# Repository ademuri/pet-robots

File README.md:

# Pet Robots

Small household robots with personality.

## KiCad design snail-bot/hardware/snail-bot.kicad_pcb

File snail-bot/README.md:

I added support for the STM32G030F6 on Arduino to Platformio in [this commit](https://github.com/stm32duino/Arduino_Core_STM32/pull/1589). That change isn't in a release yet, so you'll need to manually update it:

```bash
cd /tmp
git clone https://github.com/stm32duino/Arduino_Core_STM32
cd Arduino_Core_STM32
git checkout 8c7db46
cp ./* "${HOME?}/.platformio/packages/framework-arduinoststm32/"
```

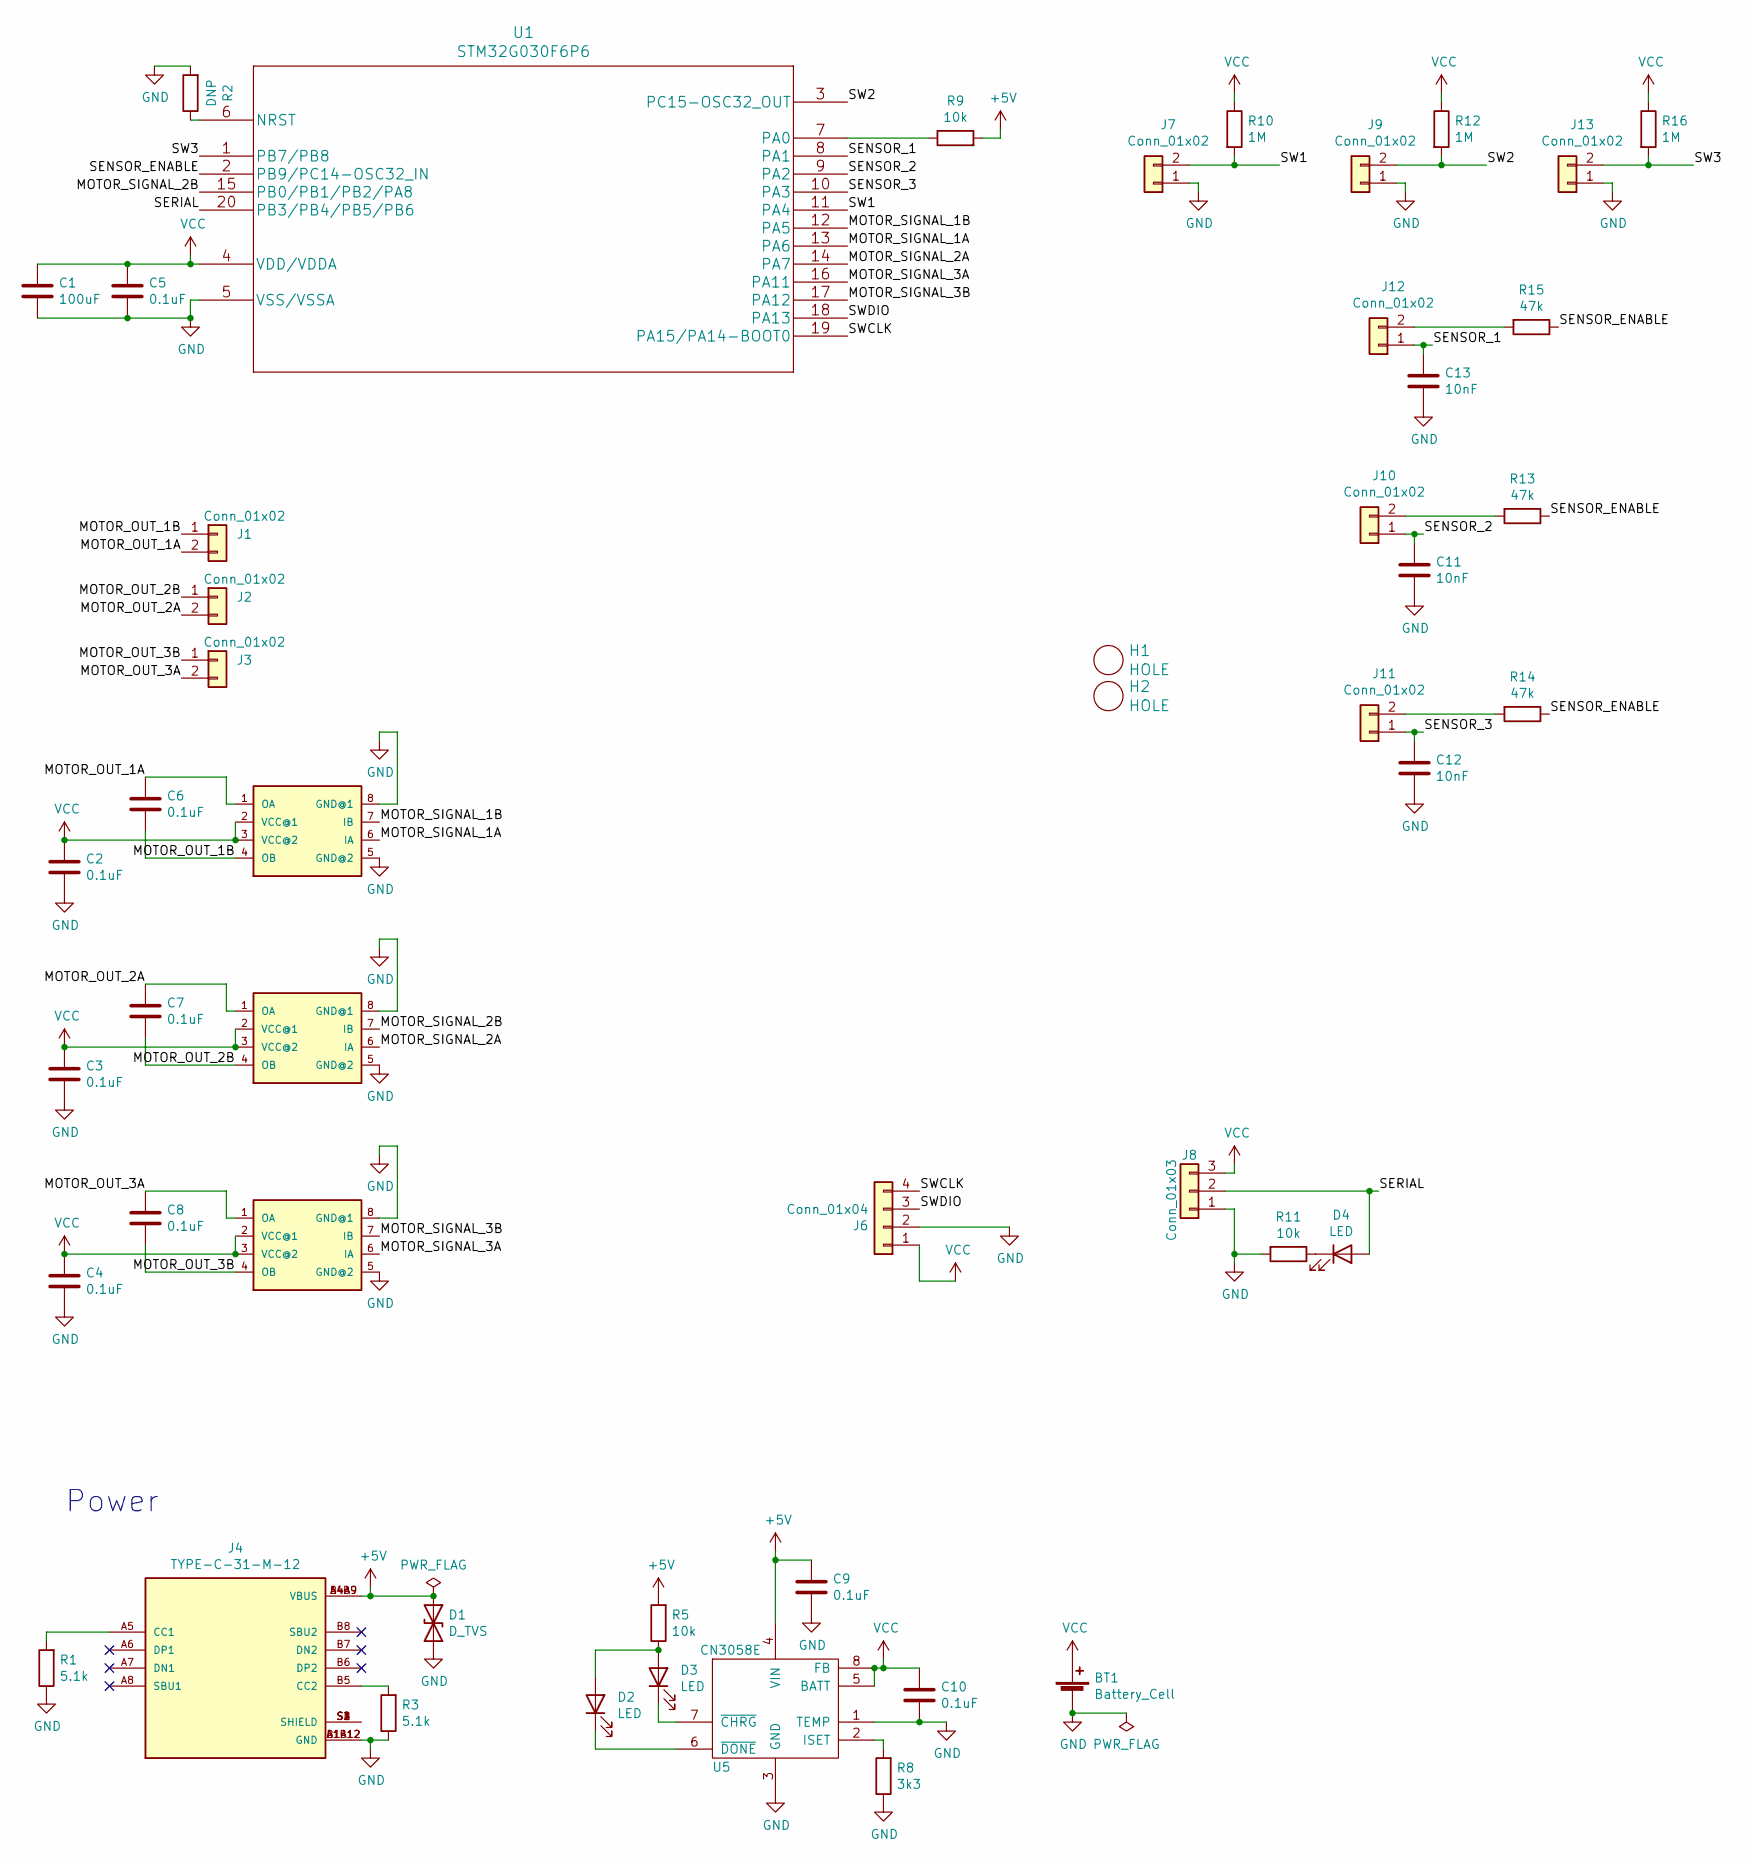
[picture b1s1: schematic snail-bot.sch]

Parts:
BT1: Battery_Cell; BatteryHolder_Keystone_2460_1xAA
C1: 100uF; C_1206_3216Metric; LCSC C15008
C2, C3, C4, C5, C6, C7, C8, C9, C10: 0.1uF; C_0603_1608Metric; LCSC C14663
C11, C12, C13: 10nF; C_0603_1608Metric; LCSC C57112
D1: D_TVS; D_SMB; LCSC C78395
D2: LED; LED_0603_1608Metric; LCSC C72043
D3, D4: LED; LED_0603_1608Metric; LCSC C2286
H1, H2: HOLE; MountingHole_3.2mm_M3
J1, J2, J3, J7, J9, J10, J11, J12, J13: Conn_01x02; JST_ZH_XKB_SMD_1x02_P1.5mm_Horizontal; LCSC C406141
J4: TYPE-C-31-M-12; HRO_TYPE-C-31-M-12; PARTREV A; LCSC C165948
J6: Conn_01x04; PinHeader_1x04_P2.54mm_Vertical
J8: Conn_01x03; PinHeader_1x03_P2.54mm_Vertical
R1, R3: 5.1k; R_0603_1608Metric; LCSC C23186
R2: DNP; R_0603_1608Metric_Pad1.05x0.95mm_HandSolder
R5, R9, R11: 10k; R_0603_1608Metric; LCSC C25804
R8: 3k3; R_0603_1608Metric; LCSC C22978
R10, R12, R16: 1M; R_0603_1608Metric; LCSC C22935
R13, R14, R15: 47k; R_0603_1608Metric; LCSC C25819
U1: STM32G030F6P6; TSSOP-20_4.4x6.5mm_P0.65mm; LCSC C529330
U2, U3, U4: L9110; SO-08; LCSC C725793
U5: CN3058E; SOP-8_3.9x4.9mm_P1.27mm_Thermal; LCSC C112011

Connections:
+5V: C9.1, D1.1 (A1), J4.A4B9 (VBUS), J4.B4A9 (VBUS), R5.2, R9.2, U5.4 (VIN)
/MOTOR_OUT_1A: C6.1, J1.2, U2.1 (OA)
/MOTOR_OUT_1B: C6.2, J1.1, U2.4 (OB)
/MOTOR_OUT_2A: C7.1, J2.2, U3.1 (OA)
/MOTOR_OUT_2B: C7.2, J2.1, U3.4 (OB)
/MOTOR_OUT_3A: C8.1, J3.2, U4.1 (OA)
/MOTOR_OUT_3B: C8.2, J3.1, U4.4 (OB)
/MOTOR_SIGNAL_1A: U1.13 (PA6), U2.6 (IA)
/MOTOR_SIGNAL_1B: U1.12 (PA5), U2.7 (IB)
/MOTOR_SIGNAL_2A: U1.14 (PA7), U3.6 (IA)
/MOTOR_SIGNAL_2B: U1.15 (PB0/PB1/PB2/PA8), U3.7 (IB)
/MOTOR_SIGNAL_3A: U1.16 (PA11), U4.6 (IA)
/MOTOR_SIGNAL_3B: U1.17 (PA12), U4.7 (IB)
/SENSOR_1: C13.1, J12.1, U1.8 (PA1)
/SENSOR_2: C11.1, J10.1, U1.9 (PA2)
/SENSOR_3: C12.1, J11.1, U1.10 (PA3)
/SENSOR_ENABLE: R13.1, R14.1, R15.1, U1.2 (PB9/PC14-OSC32_IN)
/SERIAL: D4.2 (A), J8.2, U1.20 (PB3/PB4/PB5/PB6)
/SW1: J7.2, R10.2, U1.11 (PA4)
/SW2: J9.2, R12.2, U1.3 (PC15-OSC32_OUT)
/SW3: J13.2, R16.2, U1.1 (PB7/PB8)
/SWCLK: J6.4, U1.19 (PA15/PA14-BOOT0)
/SWDIO: J6.3, U1.18 (PA13)
GND: BT1.2 (-), C1.2, C2.2, C3.2, C4.2, C5.2, C9.2, C10.2, C11.2, C12.2, C13.2, D1.2 (A2), J4.A1B12 (GND), J4.B1A12 (GND), J6.2, J7.1, J8.1, J9.1, J13.1, R1.1, R2.2, R3.1, R8.1, R11.2, U1.5 (VSS/VSSA), U2.5 (GND@2), U2.8 (GND@1), U3.5 (GND@2), U3.8 (GND@1), U4.5 (GND@2), U4.8 (GND@1), U5.1 (TEMP), U5.3 (GND)
unnamed: D2.1 (K), U5.6 (~DONE)
unnamed: D2.2 (A), D3.2 (A), R5.1
unnamed: D3.1 (K), U5.7 (~CHRG)
unnamed: D4.1 (K), R11.1
unnamed: J4.A5 (CC1), R1.2
unnamed: J4.B5 (CC2), R3.2
unnamed: J4.S1 (SHIELD), J4.S2 (SHIELD), J4.S3 (SHIELD), J4.S4 (SHIELD)
unnamed: J10.2, R13.2
unnamed: J11.2, R14.2
unnamed: J12.2, R15.2
unnamed: R2.1, U1.6 (NRST)
unnamed: R8.2, U5.2 (ISET)
unnamed: R9.1, U1.7 (PA0)
VCC: BT1.1 (+), C1.1, C2.1, C3.1, C4.1, C5.1, C10.1, J6.1, J8.3, R10.1, R12.1, R16.1, U1.4 (VDD/VDDA), U2.2 (VCC@1), U2.3 (VCC@2), U3.2 (VCC@1), U3.3 (VCC@2), U4.2 (VCC@1), U4.3 (VCC@2), U5.5 (BATT), U5.8 (FB)

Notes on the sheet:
Power

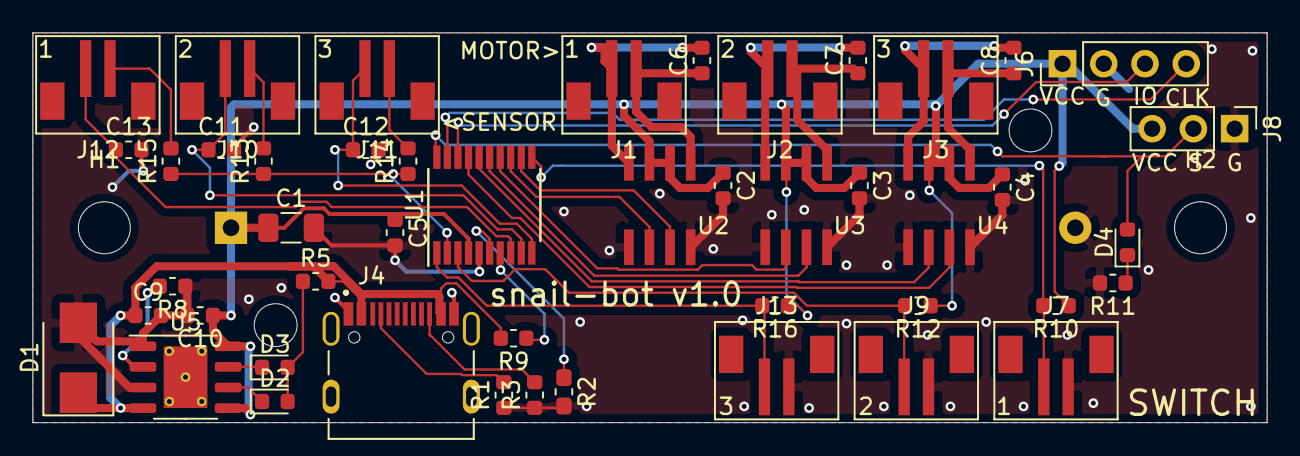
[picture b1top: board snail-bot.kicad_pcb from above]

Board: 2 copper layers, 76.0 x 24.0 mm, 50 parts (1 on the bottom side), 38 nets.

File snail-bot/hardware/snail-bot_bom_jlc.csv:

"Comment","Designator","Footprint","LCSC Part #"
"100uF","C1","C_1206_3216Metric","C15008"
"0.1uF","C5,C9,C10,C7,C6,C3,C2,C8,C4","C_0603_1608Metric","C14663"
"10nF","C12,C11,C13","C_0603_1608Metric","C57112"
"D_TVS","D1","D_SMB","C78395"
"LED","D2","LED_0603_1608Metric","C72043"
"LED","D4,D3","LED_0603_1608Metric","C2286"
"TYPE-C-31-M-12","J4","HRO_TYPE-C-31-M-12","C165948"
"Conn_01x02","J7,J9,J13,J12,J10,J11,J1,J2,J3","JST_ZH_XKB_SMD_1x02_P1.5mm_Horizontal","C406141"
"5.1k","R1,R3","R_0603_1608Metric","C23186"
"3k3","R8","R_0603_1608Metric","C22978"
"1M","R10,R12,R16","R_0603_1608Metric","C22935"
"10k","R11,R5,R9","R_0603_1608Metric","C25804"
"47k","R14,R13,R15","R_0603_1608Metric","C25819"
"STM32G030F6P6","U1","TSSOP-20_4.4x6.5mm_P0.65mm","C529330"
"L9110","U3,U2,U4","SO-08","C725793"
"CN3058E","U5","SOP-8_3.9x4.9mm_P1.27mm_Thermal","C112011"

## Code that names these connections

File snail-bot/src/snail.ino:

#include "STM32LowPower.h"

const int kLedPin = PB_3;

const int kMotor1A = PA6;
const int kMotor1B = PA5;
const int kMotor2A = PA7;
const int kMotor2B = PB0;
const int kMotor3A = PA11;
const int kMotor3B = PA12;

const int kSensorEnable = PB9;
const int kSensor1 = PA1;
const int kSensor2 = PA2;
const int kSensor3 = PA3;

const int kSwitch1 = PA4;
const int kSwitch2 = PC15;
const int kSwitch3 = PB7;

// If the device was reset via the NRST pin, just wait to be programmed.
bool pinReset;

void setup() {
  if (__HAL_RCC_GET_FLAG(RCC_FLAG_LPWRRST) || __HAL_RCC_GET_FLAG(RCC_FLAG_PWRRST) || __HAL_RCC_GET_FLAG(RCC_FLAG_SFTRST)) {
    pinReset = false;
  } else {
    pinReset = __HAL_RCC_GET_FLAG(RCC_FLAG_PINRST);
  }
  __HAL_RCC_CLEAR_RESET_FLAGS();
  pinMode(kLedPin, OUTPUT);

  pinMode(kMotor1A, OUTPUT);
  pinMode(kMotor1B, OUTPUT);
  pinMode(kMotor2A, OUTPUT);
  pinMode(kMotor2B, OUTPUT);
  pinMode(kMotor3A, OUTPUT);
  pinMode(kMotor3B, OUTPUT);
  
  pinMode(kSensorEnable, OUTPUT);
  pinMode(kSensor1, INPUT);
  pinMode(kSensor2, INPUT);
  pinMode(kSensor3, INPUT);

  pinMode(kSwitch1, INPUT);
  pinMode(kSwitch2, INPUT);
  pinMode(kSwitch3, INPUT);

  // Use a slow frequency since we're driving motors
  analogWriteFrequency(400);
  digitalWrite(kSensorEnable, HIGH);

  LowPower.begin();

  digitalWrite(kLedPin, HIGH);
  delay(500);
  digitalWrite(kLedPin, LOW);
  delay(500);

 delay(1000);
}

void loop() {
#ifdef   TEST
  test();
#else
  if (pinReset) {
    digitalWrite(kLedPin, HIGH);
    delay(100);
    digitalWrite(kLedPin, LOW);
    delay(100);
  } else {
    digitalWrite(kLedPin, HIGH);
    LowPower.deepSleep(100);
    digitalWrite(kLedPin, LOW);
    LowPower.deepSleep(3000);

    digitalWrite(kLedPin, HIGH);
    delay(300);
    digitalWrite(kLedPin, LOW);
    delay(3000);
  }
#endif
}

void test() {
  const int motorPinA = kMotor1A;
  const int motorPinB = kMotor1B;
  const int sensorPin = kSensor1;
  const int switchPin = kSwitch1;

  uint32_t light = analogRead(sensorPin);
  analogWrite(kLedPin, light);

  const uint8_t speed = 128;

  if (!digitalRead(switchPin)) {
    analogWrite(motorPinA, speed);
    digitalWrite(motorPinB, 0);
  } else {
    analogWrite(motorPinA, 256 - speed);
    digitalWrite(motorPinB, 1);
  }
  delay(5);
}

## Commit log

2021-11-17 Snail-bot schematic mostly finished
2021-11-18 Schematic polish
2021-11-18 Finish schematic and associations
2021-11-19 snail-bot v1.0
2021-11-20 Add 3D models
2021-12-12 Add blinky program for snail-bot
2021-12-12 Move snail-bot board into hardware dir
2021-12-13 Migrate to Arduino
2021-12-17 Add test sketch
2021-12-20 Finish test sketch
2021-12-20 Add license and readme
2022-01-02 Add low-power sleep (untested)
2022-01-04 Fix low-power code
    Also add logic to not go to low-power mode if the reset pin was used.
    Without this, it's annoying to reprogram.
2022-01-11 Switch to STM32LowPower library
